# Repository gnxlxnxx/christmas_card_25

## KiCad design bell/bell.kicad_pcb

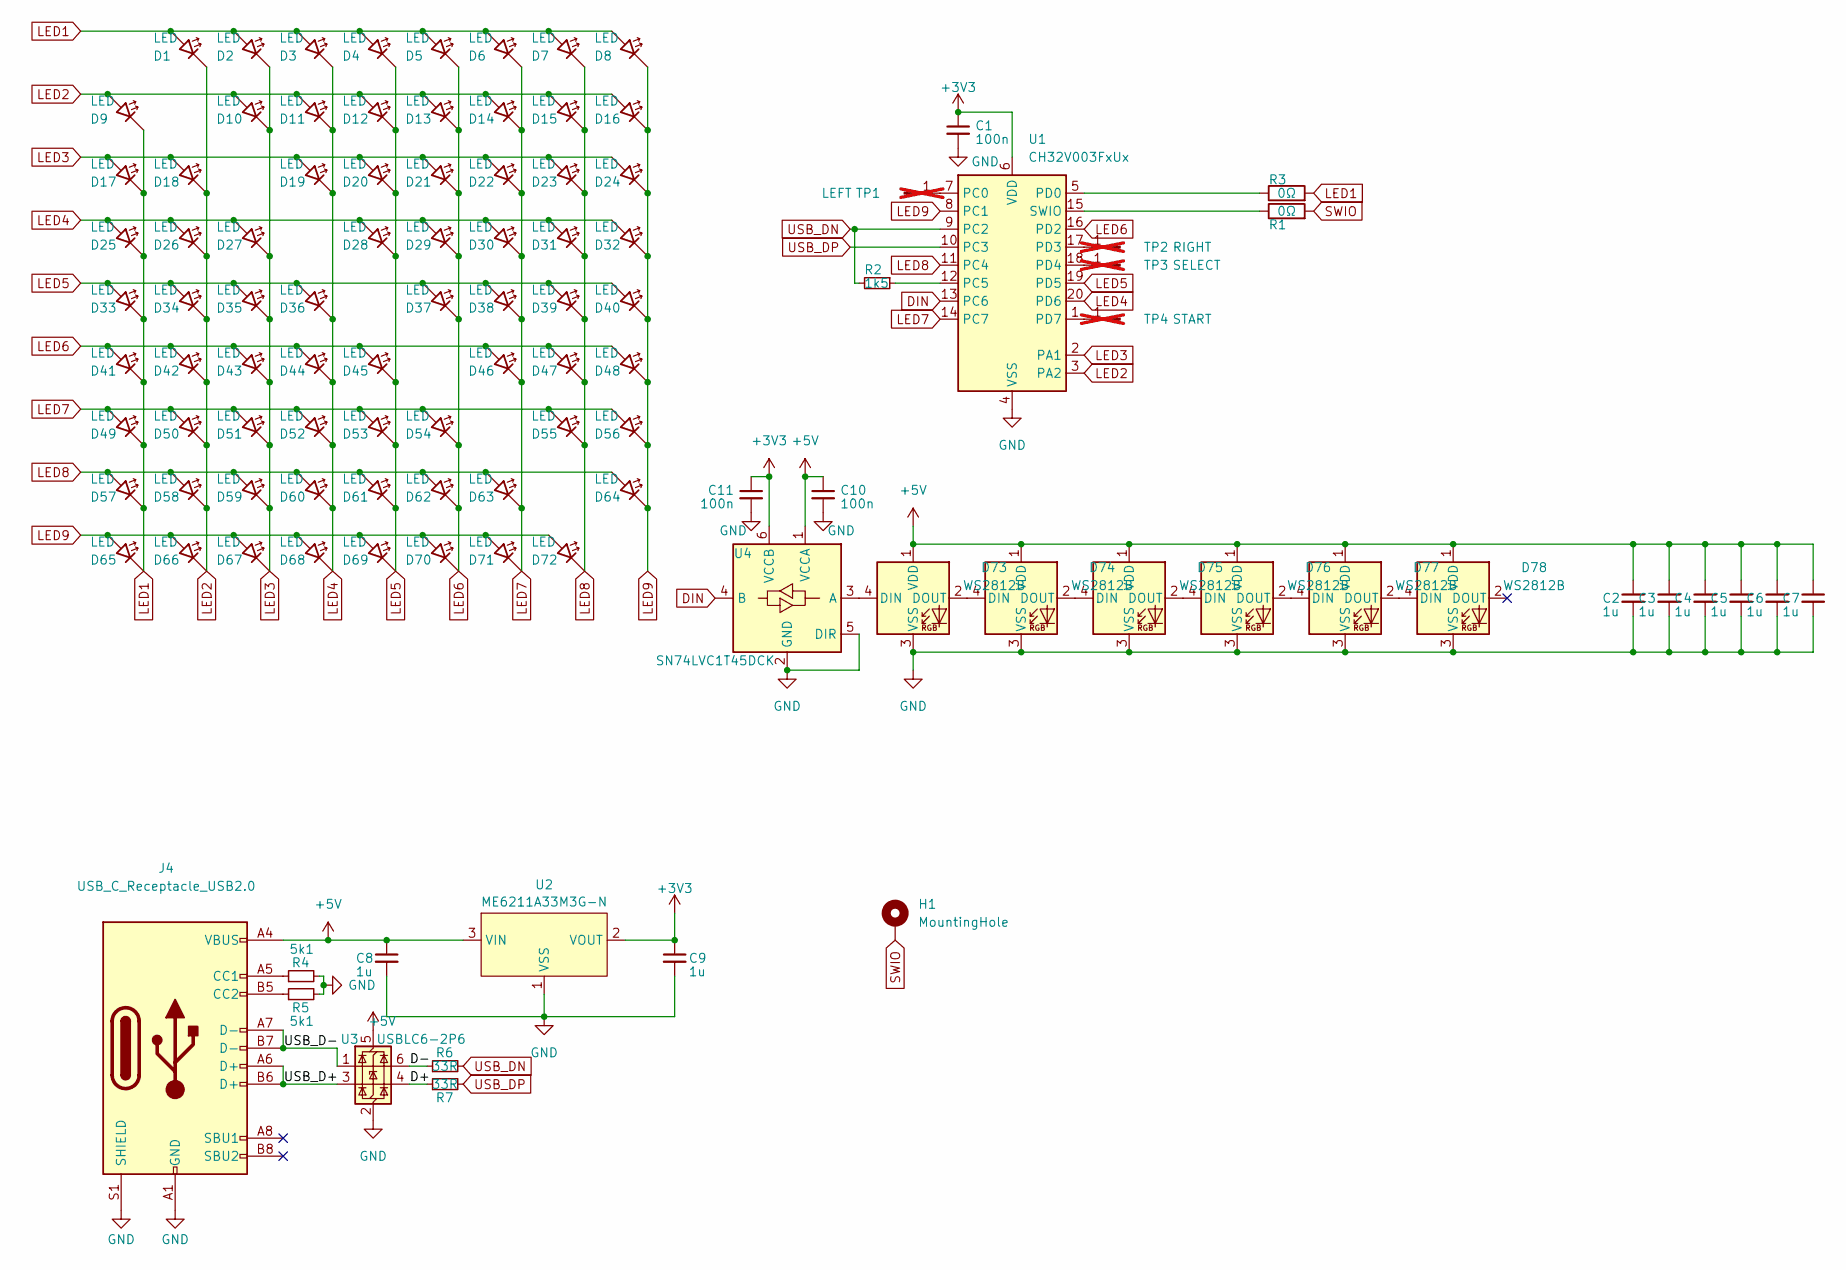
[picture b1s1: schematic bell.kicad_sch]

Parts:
C1, C10, C11: 100n; C_0402_1005Metric; LCSC C1525
C2, C3, C4, C5, C6, C7, C8, C9: 1u; C_0402_1005Metric; LCSC C52923
D1, D2, D3, D4, D5, D6, D7, D8, D9, D10, D11, D12, D13, D14, D15, D16, D17, D18, D19, D20, D21, D22, D23, D24, D25, D26, D27, D28, D29, D30, D31, D32, D33, D34, D35, D36, D37, D38, D39, D40, D41, D42, D43, D44, D45, D46, D47, D48, D49, D50, D51, D52, D53, D54, D55, D56, D57, D58, D59, D60, D61, D62, D63, D64, D65, D66, D67, D68, D69, D70, D71, D72: LED; LED_0603_1608Metric_Pad1.05x0.95mm_HandSolder; LCSC C497938
D73, D74, D75, D76, D77, D78: WS2812B; LED_WS2812B_PLCC4_5.0x5.0mm_P3.2mm; LCSC C965555
H1: MountingHole; MountingHole_3.2mm_M3_DIN965_Pad
J4: USB_C_Receptacle_USB2.0; TYPE C 16 PIN MIDDLE MOUNT CH 0.52; LCSC C2927036
R1, R3: 0Ω; R_0402_1005Metric; LCSC C17168
R2: 1k5; R_0402_1005Metric; LCSC C25867
R4, R5: 5k1; R_0402_1005Metric; LCSC C25905
R6, R7: 33R; R_0402_1005Metric; LCSC C25105
TP1: LEFT; touchbutton; not fitted
TP2: RIGHT; touchbutton; not fitted
TP3: SELECT; uni-logo; not fitted
TP4: START; uni-logo; not fitted
U1: CH32V003FxUx; QFN-20-1EP_3x3mm_P0.4mm_EP1.65x1.65mm; LCSC C5299908
U2: ME6211A33M3G-N; SOT-23-3; LCSC C168807
U3: USBLC6-2P6; SOT-666; LCSC C2827693
U4: SN74LVC1T45DCK; SOT-363_SC-70-6; LCSC C80768

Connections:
+3V3: C1.1, C9.1, C11.1, U1.6 (VDD), U2.2 (VOUT), U4.6 (VCCB)
+5V: C2.1, C3.1, C4.1, C5.1, C6.1, C7.1, C8.1, C10.1, D73.1 (VDD), D74.1 (VDD), D75.1 (VDD), D76.1 (VDD), D77.1 (VDD), D78.1 (VDD), J4.A4 (VBUS), J4.A9 (VBUS), J4.B4 (VBUS), J4.B9 (VBUS), U2.3 (VIN), U3.5 (VBUS), U4.1 (VCCA)
/D+: R7.1, U3.4 (I/O2)
/D-: R6.1, U3.6 (I/O1)
/USB_D+: J4.A6 (D+), J4.B6 (D+), U3.3 (I/O2)
/USB_D-: J4.A7 (D-), J4.B7 (D-), U3.1 (I/O1)
DIN: U1.13 (PC6), U4.4 (B)
GND: C1.2, C2.2, C3.2, C4.2, C5.2, C6.2, C7.2, C8.2, C9.2, C10.2, C11.2, D73.3 (VSS), D74.3 (VSS), D75.3 (VSS), D76.3 (VSS), D77.3 (VSS), D78.3 (VSS), J4.A1 (GND), J4.A12 (GND), J4.B1 (GND), J4.B12 (GND), J4.S1 (SHIELD), R4.2, R5.2, U1.4 (VSS), U1.21 (VSS), U2.1 (VSS), U3.2 (GND), U4.2 (GND), U4.5 (DIR)
LED1: D1.2 (A), D2.2 (A), D3.2 (A), D4.2 (A), D5.2 (A), D6.2 (A), D7.2 (A), D8.2 (A), D9.1 (K), D17.1 (K), D25.1 (K), D33.1 (K), D41.1 (K), D49.1 (K), D57.1 (K), D65.1 (K), R3.2
LED2: D1.1 (K), D9.2 (A), D10.2 (A), D11.2 (A), D12.2 (A), D13.2 (A), D14.2 (A), D15.2 (A), D16.2 (A), D18.1 (K), D26.1 (K), D34.1 (K), D42.1 (K), D50.1 (K), D58.1 (K), D66.1 (K), U1.3 (PA2)
LED3: D2.1 (K), D10.1 (K), D17.2 (A), D18.2 (A), D19.2 (A), D20.2 (A), D21.2 (A), D22.2 (A), D23.2 (A), D24.2 (A), D27.1 (K), D35.1 (K), D43.1 (K), D51.1 (K), D59.1 (K), D67.1 (K), U1.2 (PA1)
LED4: D3.1 (K), D11.1 (K), D19.1 (K), D25.2 (A), D26.2 (A), D27.2 (A), D28.2 (A), D29.2 (A), D30.2 (A), D31.2 (A), D32.2 (A), D36.1 (K), D44.1 (K), D52.1 (K), D60.1 (K), D68.1 (K), U1.20 (PD6)
LED5: D4.1 (K), D12.1 (K), D20.1 (K), D28.1 (K), D33.2 (A), D34.2 (A), D35.2 (A), D36.2 (A), D37.2 (A), D38.2 (A), D39.2 (A), D40.2 (A), D45.1 (K), D53.1 (K), D61.1 (K), D69.1 (K), U1.19 (PD5)
LED6: D5.1 (K), D13.1 (K), D21.1 (K), D29.1 (K), D37.1 (K), D41.2 (A), D42.2 (A), D43.2 (A), D44.2 (A), D45.2 (A), D46.2 (A), D47.2 (A), D48.2 (A), D54.1 (K), D62.1 (K), D70.1 (K), U1.16 (PD2)
LED7: D6.1 (K), D14.1 (K), D22.1 (K), D30.1 (K), D38.1 (K), D46.1 (K), D49.2 (A), D50.2 (A), D51.2 (A), D52.2 (A), D53.2 (A), D54.2 (A), D55.2 (A), D56.2 (A), D63.1 (K), D71.1 (K), U1.14 (PC7)
LED8: D7.1 (K), D15.1 (K), D23.1 (K), D31.1 (K), D39.1 (K), D47.1 (K), D55.1 (K), D57.2 (A), D58.2 (A), D59.2 (A), D60.2 (A), D61.2 (A), D62.2 (A), D63.2 (A), D64.2 (A), D72.1 (K), U1.11 (PC4)
LED9: D8.1 (K), D16.1 (K), D24.1 (K), D32.1 (K), D40.1 (K), D48.1 (K), D56.1 (K), D64.1 (K), D65.2 (A), D66.2 (A), D67.2 (A), D68.2 (A), D69.2 (A), D70.2 (A), D71.2 (A), D72.2 (A), U1.8 (PC1)
unnamed: D73.4 (DIN), U4.3 (A)
unnamed: D73.2 (DOUT), D74.4 (DIN)
unnamed: D74.2 (DOUT), D75.4 (DIN)
unnamed: D75.2 (DOUT), D76.4 (DIN)
unnamed: D76.2 (DOUT), D77.4 (DIN)
unnamed: D77.2 (DOUT), D78.4 (DIN)
unnamed: J4.A5 (CC1), R4.1
unnamed: J4.B5 (CC2), R5.1
unnamed 25: TP1.1, U1.7 (PC0); also elsewhere on the board
unnamed 26: TP2.1, U1.17 (PD3); also elsewhere on the board
unnamed: TP3.1, U1.18 (PD4)
unnamed: TP4.1, U1.1 (PD7)
unnamed: R2.1, U1.12 (PC5)
unnamed: R3.1, U1.5 (PD0)
unnamed: R1.1, U1.15 (SWIO)
SWIO: H1.1, R1.2
USB_DN: R2.2, R6.2, U1.9 (PC2)
USB_DP: R7.2, U1.10 (PC3)

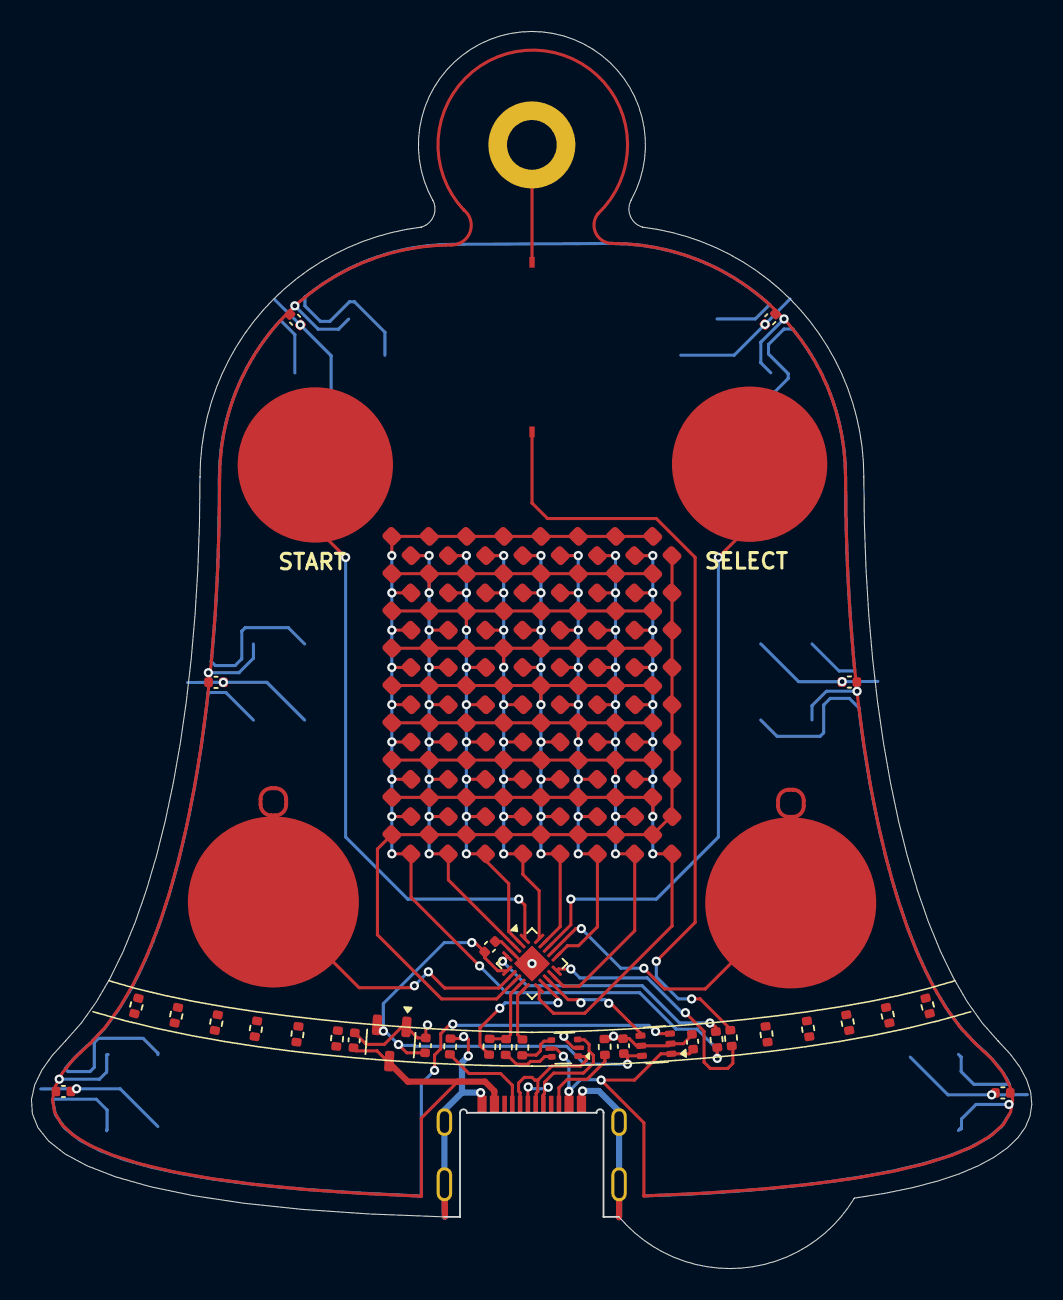
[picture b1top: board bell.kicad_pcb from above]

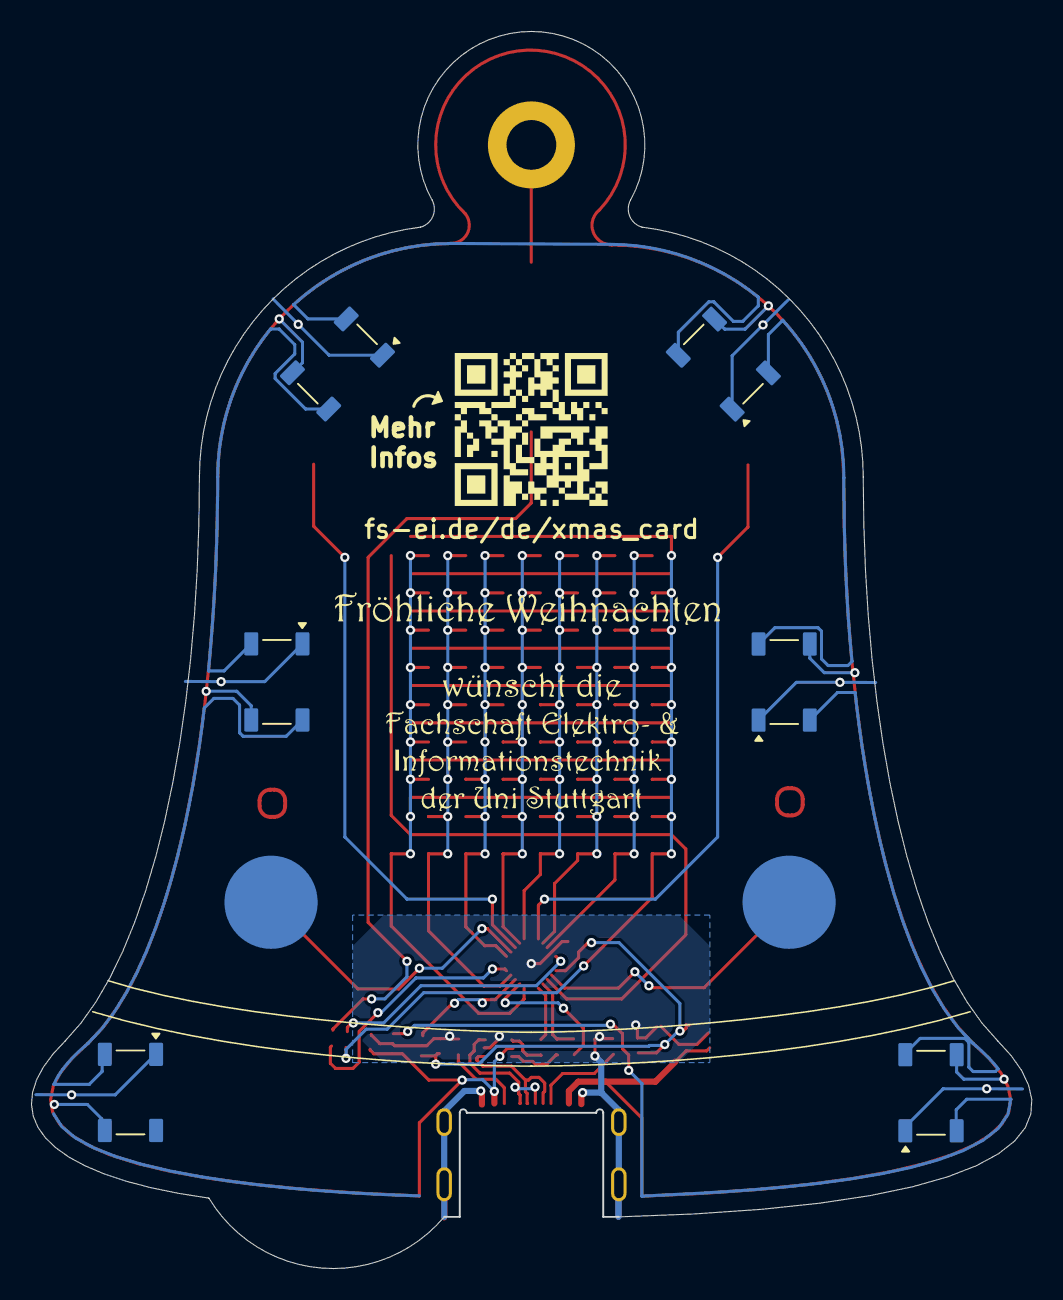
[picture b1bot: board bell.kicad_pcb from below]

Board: 2 copper layers, 64.3 x 79.6 mm, 119 parts (8 on the bottom side), 35 nets.

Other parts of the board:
J6, J6#2: Touchpad1; touch_pad
R10, R11, R12, R13, R14, R15, R16, R17, R18, R19, R20: 0Ω; R_0402_1005Metric
TP10: RIGHT; touchbutton
TP10#2: LEFT; touchbutton

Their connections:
unnamed 25: J6#2.1; also elsewhere on the board
unnamed 26: J6.1; also elsewhere on the board

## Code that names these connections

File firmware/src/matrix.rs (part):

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
impl<'a> LedPins<'a> {
    pub fn new(
        led1: Peri<'a, peripherals::PD0>,
        led2: Peri<'a, peripherals::PA2>,
        led3: Peri<'a, peripherals::PA1>,
        led4: Peri<'a, peripherals::PD6>,
        led5: Peri<'a, peripherals::PD5>,
        led6: Peri<'a, peripherals::PD2>,
        led7: Peri<'a, peripherals::PC7>,
        led8: Peri<'a, peripherals::PC4>,
        led9: Peri<'a, peripherals::PC1>
    ) -> Self {
        // Set all pins high
        pac::GPIOA.bshr().write(|w| {
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
#[derive(Debug)]
pub struct ButtonPins<'a> {
    start: Peri<'a, peripherals::PD7>,
    select: Peri<'a, peripherals::PD4>,
    l: Peri<'a, peripherals::PC0>,
    r: Peri<'a, peripherals::PD3>
}

impl<'a> ButtonPins<'a> {
    pub fn new(
        start: Peri<'a, peripherals::PD7>,
        select: Peri<'a, peripherals::PD4>,
        l: Peri<'a, peripherals::PC0>,
        r: Peri<'a, peripherals::PD3>
    ) -> Self {
        Self { start, select, l, r }
    }
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
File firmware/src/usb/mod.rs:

pub mod descriptors;
pub mod usb;
use crate::drivers::buttons::{Button, Buttons};
use crate::hal;
use crate::hal::{gpio::Pin, pac, peripherals::*, Peri};

use usb::UsbIf;

pub fn init(
    dp: Peri<'static, PC3>,
    dm: Peri<'static, PC2>,
    afio: &mut hal::pac::afio::Afio,
    exti: &mut hal::pac::exti::Exti,
    systick: &mut hal::pac::systick::Systick,
) -> UsbIf<0x4001_1000usize, 3, 2, 3> {
    systick.ctlr().write(|w| {
        w.set_stclk(pac::systick::vals::Stclk::HCLK);
        w.set_ste(true);
    });

    let mut _usb_dp = hal::gpio::Input::new(dp, hal::gpio::Pull::None);
    let pin_number = dm.pin() as usize;
    let port_number = dm.port();
    let mut _usb_dm = hal::gpio::Input::new(dm, hal::gpio::Pull::None);
    let usb_if = UsbIf::new(
        |_e, _scratchpad, endp, sendtok, usbif| {
            if endp == 1 {
                let mut tsajoystick_keyboard: [u8; 8] = [0x00; 8];
                let mut nextkc = tsajoystick_keyboard.iter_mut().skip(2);
                // Keyboard (8 bytes)
                if Buttons::get(Button::R) {
                    *nextkc.next().unwrap() = 0x4f; // Right
                }
                if Buttons::get(Button::L) {
                    *nextkc.next().unwrap() = 0x50; // Left
                }
                unsafe {
                    usbif.usb_send_data(tsajoystick_keyboard.as_ptr(), 8, 0, sendtok);
                }
            } else {
                // If it's a control transfer, empty it.
                usbif.usb_send_empty(sendtok);
            }
        },
        descriptors::get_descriptor_info,
    );

    afio.exticr()
        .modify(|w| w.set_exti(pin_number, port_number));
    //Warning: The interrupts perform HSI trimming and should run with 48MHz HSI settings
    exti.intenr().write(|w| w.set_mr(pin_number, true)); // enable interrupt
    exti.ftenr().write(|w| w.set_tr(pin_number, true));
    exti.rtenr().write(|w| w.set_tr(pin_number, false));
    afio.exticr()
        .modify(|w| w.set_exti(pin_number, port_number));
    usb_if
}

pub fn usb_up(dpu: Peri<'static, PC5>) {
    let mut usb_dpu = hal::gpio::Output::new(dpu, hal::gpio::Level::Low, hal::gpio::Speed::High);

    usb_dpu.set_high();
}

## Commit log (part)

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2025-12-08 export schematic as pdf
2025-12-18 Get first matrix prototype to work
    Better start commiting now, before I accidently break it during cleanup
2025-12-18 Improve matrix
2025-12-19 Get matrix into a well-working state
2025-12-19 Fix input capturing
    Somewhere, hidden deep within the CH32V003 Reference Manual:
    > Note: Compare Capture Channel 2 is writable only
    > when the channel is off (when CC2E is zero).
2025-12-20 Optimize timer ISR
2025-12-20 Use embassy
2025-12-20 Finish button driver
2025-12-20 run rustfmt
2025-12-20 Refactor timer driver
2025-12-20 add ws2812 leds
2025-12-20 Optimize ws2812
2025-12-20 Add different ws2812 modes
    Copied from last year and oxidized
2025-12-20 Implement scrolling text
2025-12-20 Improve font
2025-12-20 Some tests
2025-12-20 `rand`om changes
2025-12-21 Add stuff to build the bootloader
2025-12-22 let rustfmt fmt rust
2025-12-22 remove for loop and unnecessary mut
2025-12-22 Move Ws2812 Modes in to seperate files
2025-12-23 Add Matrix Animation Modes
    just copied them over from last year and oxidized them
2025-12-23 use global lfsr
    this makes it at least a little bit more "random"
2025-12-23 Add preliminary snake
2025-12-26 Improve
2025-12-26 Partially revert "let rustfmt fmt rust"
    This partially reverts commit e5f715a7ef2ec48d02010a38eb5dfb876be6f6d2.
2025-12-26 Move app stuff to app directory
2025-12-26 Fit matrix and ws2812 leds for star
2025-12-26 Add alternative pin mapping
2025-12-26 Do cool stuff and then fuck it up again
2025-12-26 Remove not working auto mode
2025-12-26 Implement auto mode in a less resource intensive way
2025-12-26 Optimize matrix animations
2025-12-26 Cleanup
2025-12-26 Revert size regressing code improvement
2025-12-26 Move button sample processing to interrupt in order to save flash
2025-12-27 Remove comment
2025-12-27 Fix sparkle animation
2025-12-27 Optimize animations
2025-12-27 Begin migrating ws2812 to looped animations
2025-12-28 Improve ws2812 animations
2025-12-28 Cleanup and formatting
2025-12-29 Add new EXTI7_0_IRQHandler
2025-12-29 Add dependencies for USB
2025-12-29 Further develop snake
2025-12-29 Add USB (non-working)
2025-12-30 Replace bloated embassy sync structures through custom spinloop based ones
2025-12-30 Fix ws2812/snowball
2025-12-30 Use forked ch32-hal repo with patched out wakers
2025-12-30 Get USB working
2025-12-30 Make USB nice
2025-12-30 Implement basic snake
2025-12-31 Add endscreen for snake
2025-12-31 Implement speedhack
2026-01-01 Improve timer driver
2026-01-01 Get usb stack to run initially
2026-01-02 Update USB descriptors, remove mouse
2026-01-02 Optimize USB code
    Saves ~200 bytes
2026-01-03 Move to hand-coded DMA
2026-01-03 Fix animations for faster ws2812
    Needs some good taste applied
2026-01-03 Re-add interrupt priority setting
2026-01-03 Rework text utilities
    Saves ~250 bytes
2026-01-03 Add our own custom memcpy and memset
    Saves slightly less than 500 bytes
2026-01-05 Add Tetris
2026-01-06 Prepare usb left/right presenter input
2026-01-08 Use common show_score function for both games
2026-01-08 Add game menu
2026-01-08 Add usb left right functionality
2026-01-08 Fix text not rendering lowest two rows
2026-01-08 Add flash backed highscore
2026-01-08 Improve highscore feature
2026-01-08 Make text smaller
2026-01-08 Use registers directly for timer configuration
2026-01-08 Remove dma interrupt
2026-01-08 Fix leds being slightly turned on that shouldn’t
2026-01-08 Reduce size of show_score
2026-01-09 Enable full message again
2026-01-09 Disable ch32-hal rt feature
2026-01-09 Use ch32-hal variant without dma init
2026-01-09 Put ws2812 buf on stack
2026-01-09 Move usb code to drivers module
2026-01-09 Rename linker scripts
2026-01-09 Allow rotation in both directions in tetris
2026-01-09 Remove unnecessary premature "optimizations"
    Saves 4 bytes, interestingly enough
2026-01-09 Move tetris board to boolean
2026-01-09 Halve sine table by using the symmetrical properties of sine
    Saves ~100 bytes
    Further halving didn't save anything in my testing
2026-01-09 Use writes instead of modify, if unnecessary
2026-01-09 Move tetris board to u8 as row
    Saves exactly 100 bytes
2026-01-09 Remove all warnings
2026-01-09 Move to 8 bit gamma
    Saves ... ~256 bytes! What a surprise!
2026-01-09 Increase button sensitivity
2026-01-10 Add pong
2026-01-11 Finish pong
2026-01-11 Do some cleanup
2026-01-11 Remove pause in game menu
2026-01-11 Allow ccw rotation in tetris
2026-01-11 Implement backwards button for game menu
2026-01-11 Optimize button event passing
2026-01-11 Add ws2812 button animation for game app
2026-01-11 Cleanup codebase
2026-01-11 Improve font handling
2026-01-11 Make pong increase speed with each hit
2026-01-11 Remap game menu buttons
2026-01-11 Improve alzheimers issues
2026-01-11 Make dma (hopefully) safe and sound
2026-01-11 Simplify dma function
2026-01-12 Compress GAMMA_LUT
2026-01-12 Decrease button sensitivity to prevent phantom input
2026-01-12 Add const assertion to matrix::rand_pulse
2026-01-12 Add quadratic score behaviour to tetris
2026-01-12 End tetris only when next piece cannot be spawned
2026-01-12 Hopefully fix flash issues
2026-01-12 Show previous high score
2026-01-12 Nerf snake score multiplier
2026-01-12 Add const assertions
2026-01-12 Formatting
2026-01-12 Optimize for loops
2026-01-12 Allow out of bounds rotation at the top of the board in tetris
2026-01-13 Lower snake score multiplier limit
2026-01-21 Manually initialize clocks
2026-01-21 Remove hal usage from ws2812
2026-01-21 Remove hal usage from usb
2026-01-21 Completely remove ch32_hal dependency
2026-01-21 Save space by using u8 for port/pin ids
2026-01-21 Remove unused embedded-hal dependency
2026-01-21 Patch embassy-time
2026-01-22 Migrate embassy-time to 32bit
2026-01-22 Allow modification of Ticker duration
2026-01-24 Get rid of async usage in animations
2026-01-25 Get rid of async usage in games
2026-01-25 Fix small bugs from non-async conversion
2026-01-25 Run cargo update
2026-01-25 Fmt, clippy, remove unused dependencies etc.
2026-01-25 Optimize tetris drawing
2026-01-25 Optimize usb callback
2026-01-25 Add four in a row
2026-01-25 Implement limit animation for four in a row
2026-03-15 Discard button events during pong score screen
2026-03-15 Inline matrix access
2026-03-15 Finish four in a row
2026-03-15 Formatting and clippy
